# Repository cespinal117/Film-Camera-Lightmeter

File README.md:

# Film-Camera-Lightmeter
A PCB I designed to integrate a light meter onto my film camera.  
My inspiration for this was when I got my first film camera, a Cannon AE-1, I noticed the built-in light-meter was broken.  
For most of my time, I have been using my phone with a light-meter app to adjust my camera settings but that got annoying quick. 
Since I wanted to practice more PCB design, I figured the best way to get practice in and solve my issue is to make my own light meter and manufacture a PCB for it.

## PCB Features
 - Raspberry Pi Pico MCU
 - VEML7700-TR Ambient Light Sensor
 - Lipo battery charging circuit
 - Button control inputs
 - Automatic switching between USB power & Battery power
 - Static Discharge protection

## PCB Design

The PCB is a 2-layer board to minimize cost.  

It uses a Raspberry Pi Pico MCU as it was a relatively new board I was trying to learn to use. 
To power it, you can supply either USB-C for development, or a 3.7V Lipo battery.

It is still a WIP and I hope to have it manufactured soon.

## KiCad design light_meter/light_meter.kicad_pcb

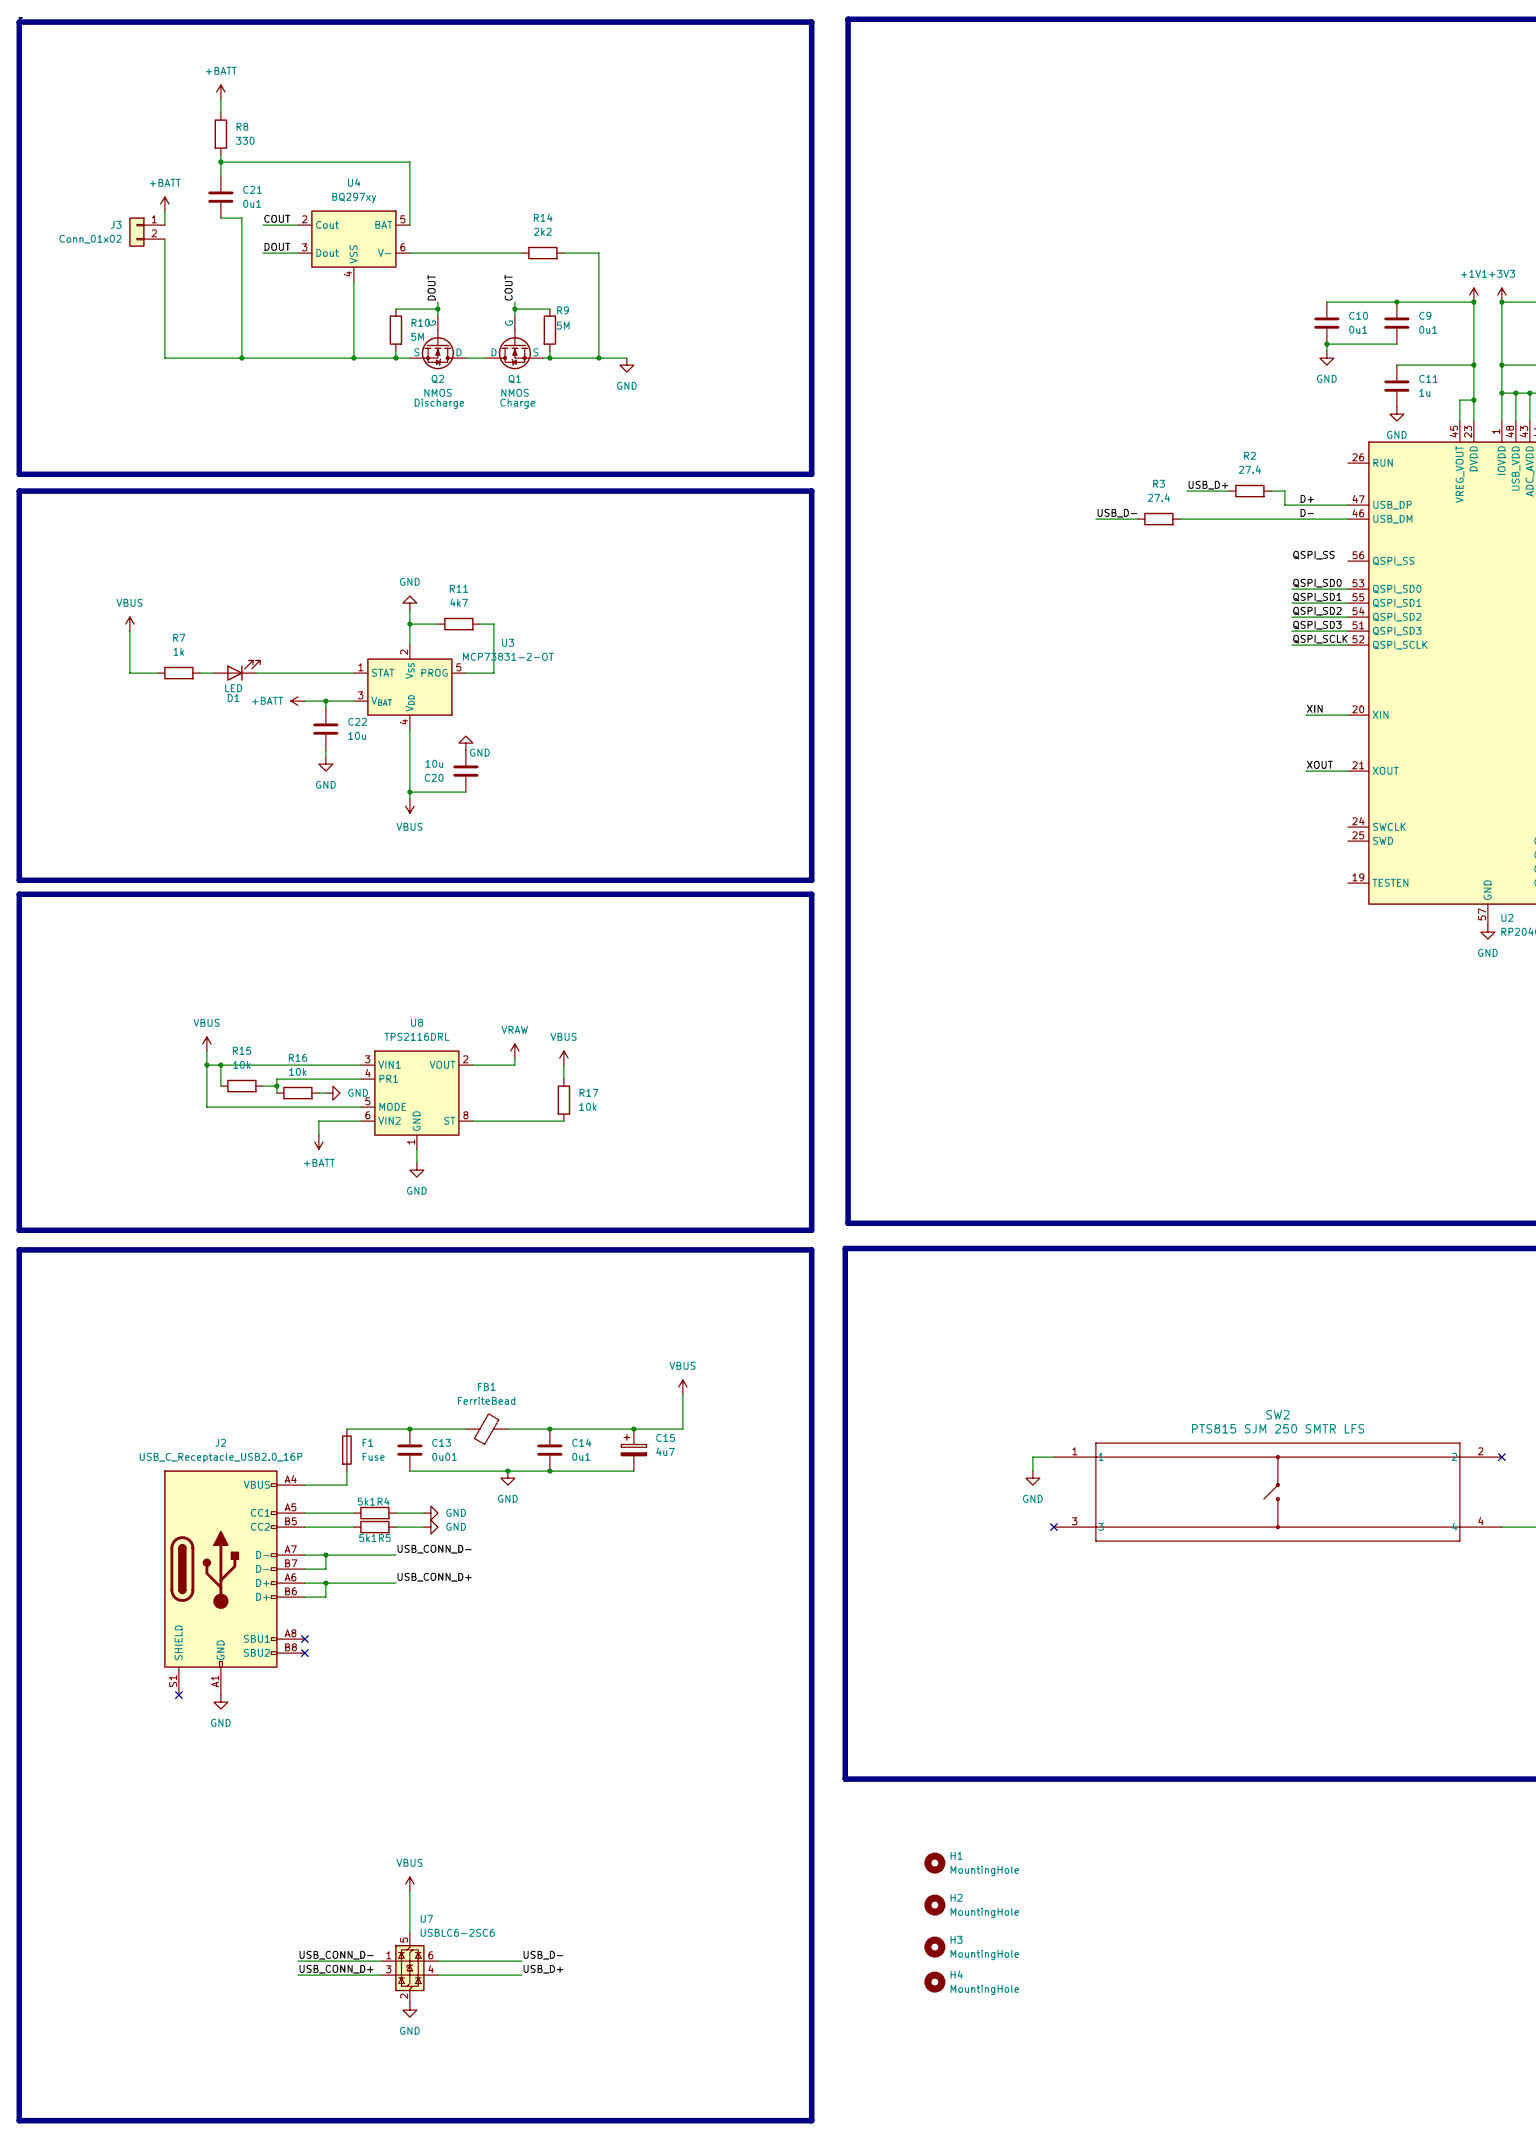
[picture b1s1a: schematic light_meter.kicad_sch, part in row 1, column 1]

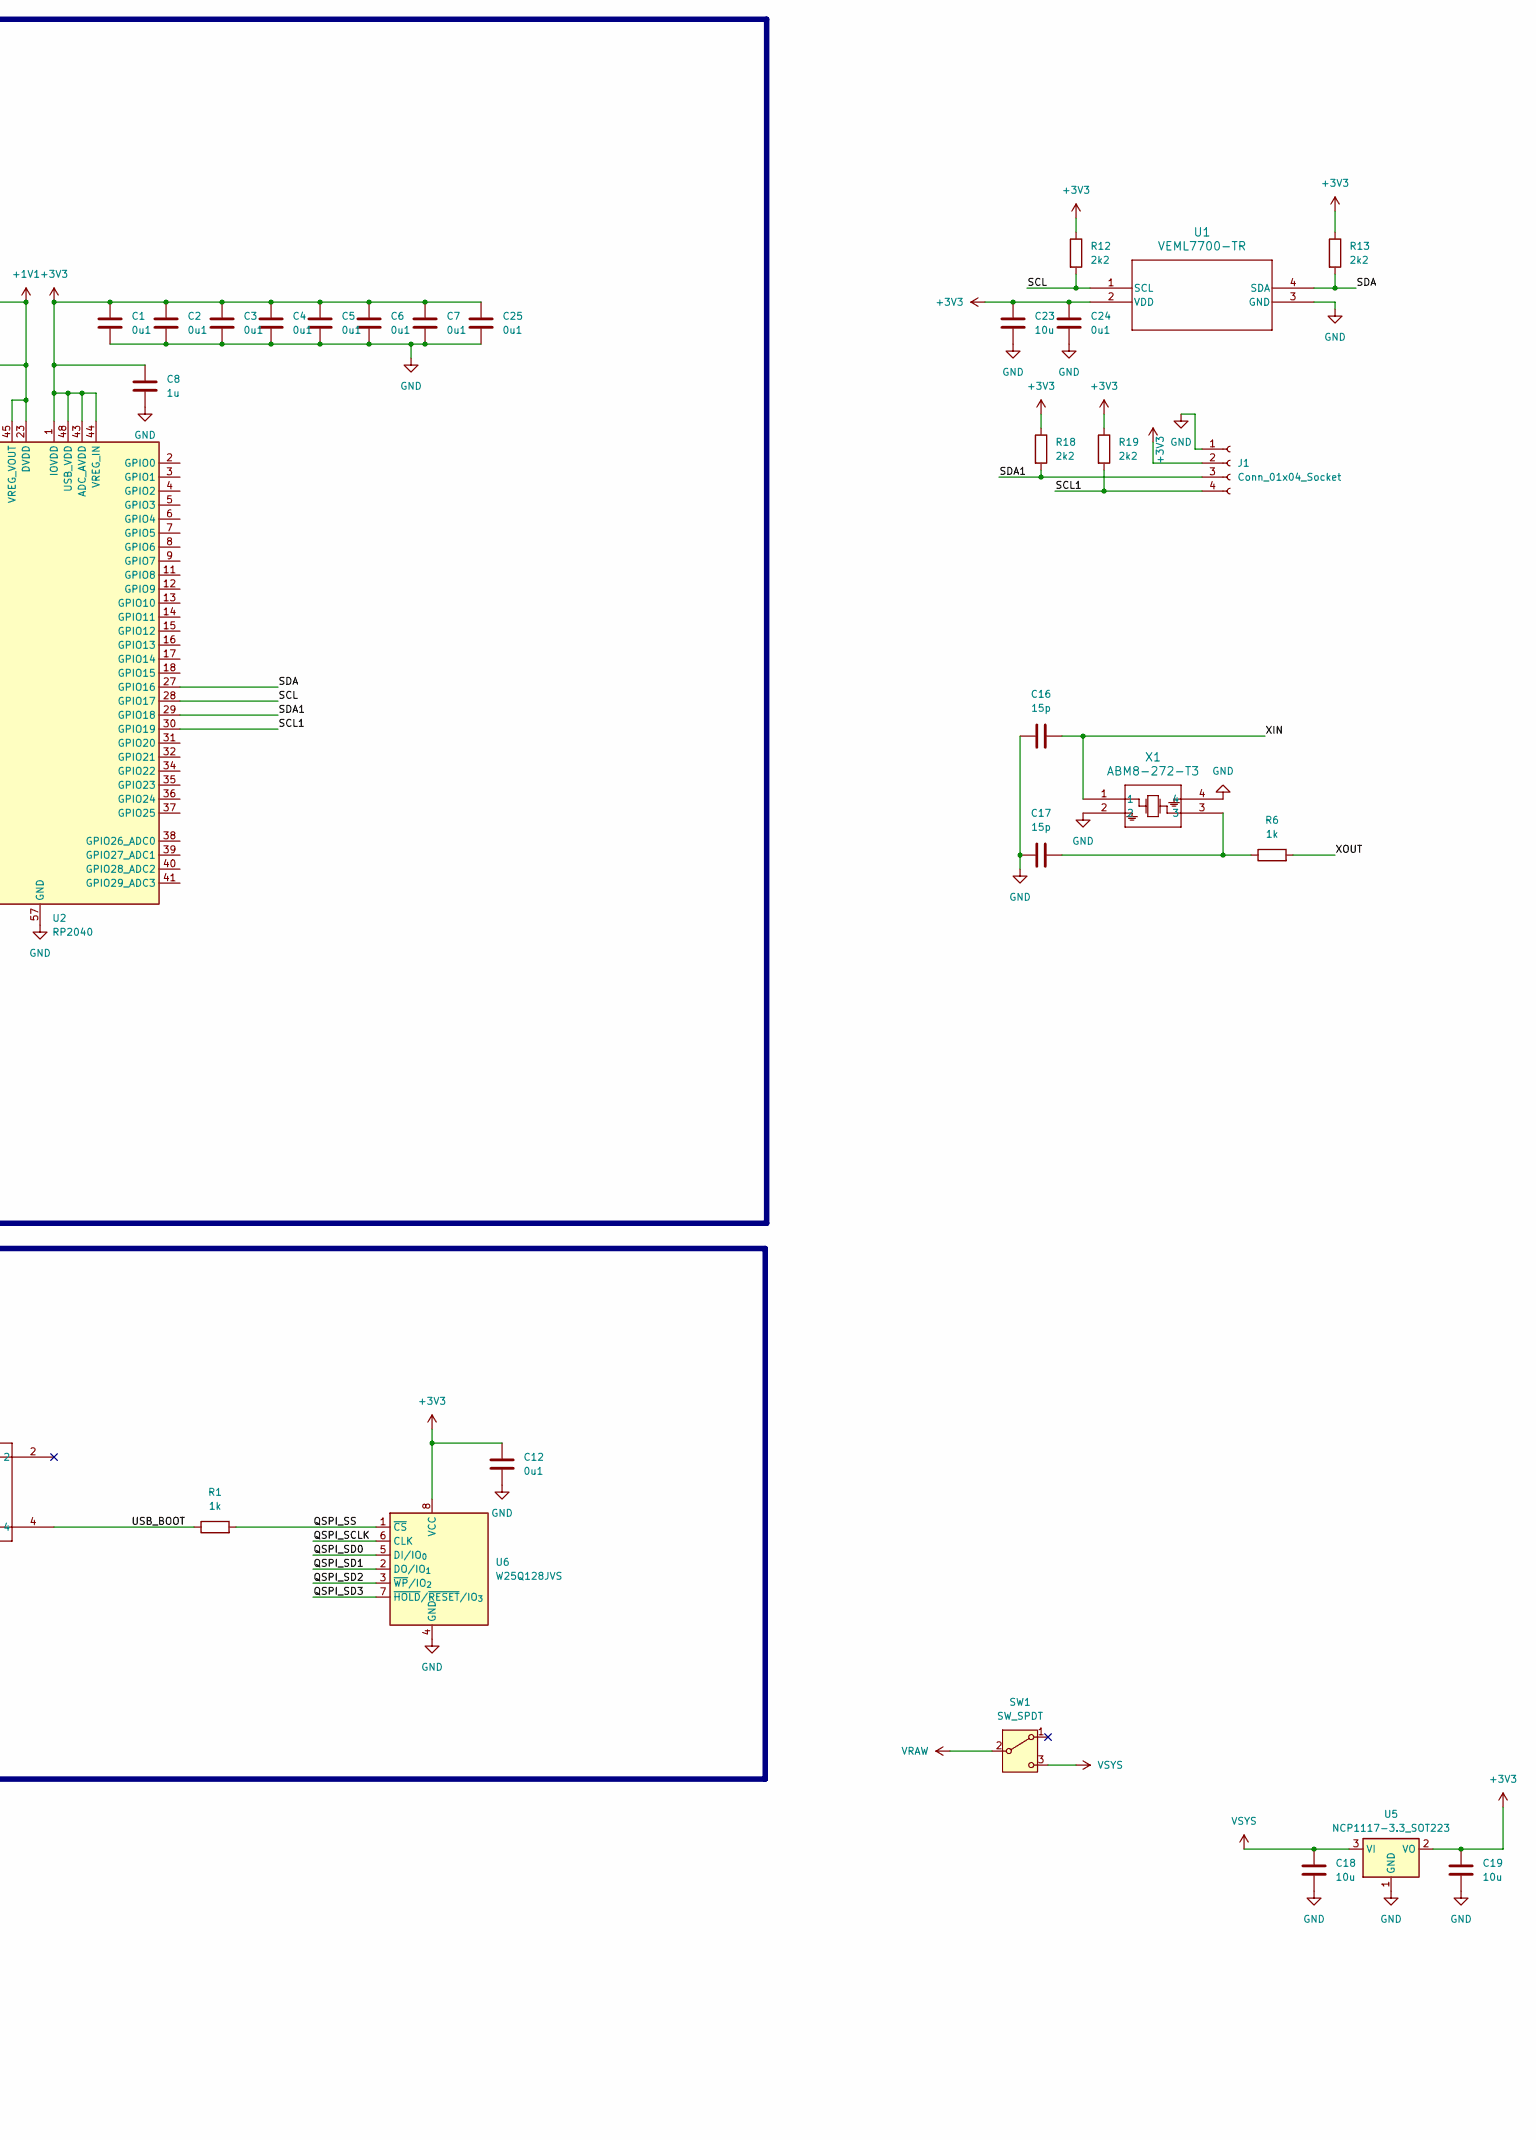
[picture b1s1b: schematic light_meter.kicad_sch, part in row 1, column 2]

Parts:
C1, C2, C3, C4, C5, C6, C7, C9, C10, C12, C14, C21, C24, C25: 0u1; C_0402_1005Metric
C8, C11: 1u; C_0402_1005Metric
C13: 0u01; C_0402_1005Metric
C15: 4u7; CP_Elec_4x5.7
C16, C17: 15p; C_0402_1005Metric
C18, C19, C20, C22: 10u; C_0603_1608Metric
C23: 10u; C_0402_1005Metric
D1: LED; LED_0603_1608Metric
F1: Fuse; Fuse_1812_4532Metric
FB1: FerriteBead; L_0603_1608Metric
H1, H2, H3, H4: MountingHole; MountingHole_2.2mm_M2
J1: Conn_01x04_Socket; JST_SH_SM04B-SRSS-TB_1x04-1MP_P1.00mm_Horizontal
J2: USB_C_Receptacle_USB2.0_16P; USB_C_Receptacle_GCT_USB4085; Part Number 2073-USB4085-GF-ATR-ND
J3: Conn_01x02; CONN_S2B-PH-K-S_JST; part number 455-1719-ND
Q1, Q2: NMOS; SOT-23-3
R1, R6: 1k; R_0402_1005Metric
R2, R3: 27.4; R_0402_1005Metric
R4, R5: 5k1; R_0402_1005Metric
R7: 1k; R_0603_1608Metric
R8: 330; R_0603_1608Metric
R9, R10: 5M; R_0402_1005Metric
R11: 4k7; R_0603_1608Metric
R12, R13, R18, R19: 2k2; R_0402_1005Metric
R14: 2k2; R_0603_1608Metric
R15, R16, R17: 10k; R_0603_1608Metric
SW1: SW_SPDT; SW_L102021ML04Q; digikey CKC5102-ND
SW2: PTS815 SJM 250 SMTR LFS; SW4_PTS815 SJM 250 SMTR LFS_CNK
U1: VEML7700-TR
U2: RP2040; QFN-56-1EP_7x7mm_P0.4mm_EP3.2x3.2mm
U3: MCP73831-2-OT; SOT-23-5
U4: BQ297xy; WSON-6_1.5x1.5mm_P0.5mm
U5: NCP1117-3.3_SOT223; SOT-223-3_TabPin2
U6: W25Q128JVS; SOIC-8_5.3x5.3mm_P1.27mm
U7: USBLC6-2SC6; SOT-23-6
U8: TPS2116DRL; SOT-583-8
X1: ABM8-272-T3; ABM8-272-T3_ABR

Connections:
+1V1: C9.1, C10.1, C11.1, U2.23 (DVDD), U2.45 (VREG_VOUT), U2.50 (DVDD)
+3V3: C1.1, C2.1, C3.1, C4.1, C5.1, C6.1, C7.1, C8.1, C12.1, C19.1, C23.1, C24.1, C25.1, J1.2, R12.1, R13.1, R18.1, R19.1, U1.2 (VDD), U2.1 (IOVDD), U2.10 (IOVDD), U2.22 (IOVDD), U2.33 (IOVDD), U2.42 (IOVDD), U2.43 (ADC_AVDD), U2.44 (VREG_IN), U2.48 (USB_VDD), U2.49 (IOVDD), U5.2 (VO), U6.8 (VCC)
+BATT: C22.1, J3.1, R8.1, U3.3 (V_{BAT}), U8.6 (VIN2)
/COUT: Q1.2 (G), R9.1, U4.2 (Cout)
/D+: R2.2, U2.47 (USB_DP)
/D-: R3.2, U2.46 (USB_DM)
/DOUT: Q2.2 (G), R10.1, U4.3 (Dout)
/QSPI_SCLK: U2.52 (QSPI_SCLK), U6.6 (CLK)
/QSPI_SD0: U2.53 (QSPI_SD0), U6.5 (DI/IO_{0})
/QSPI_SD1: U2.55 (QSPI_SD1), U6.2 (DO/IO_{1})
/QSPI_SD2: U2.54 (QSPI_SD2), U6.3 (~WP/IO_{2})
/QSPI_SD3: U2.51 (QSPI_SD3), U6.7 (~HOLD/~RESET/IO_{3})
/QSPI_SS: R1.2, U6.1 (~CS)
/SCL: R12.2, U1.1 (SCL), U2.28 (GPIO17)
/SCL1: J1.4, R19.2, U2.30 (GPIO19)
/SDA: R13.2, U1.4 (SDA), U2.27 (GPIO16)
/SDA1: J1.3, R18.2, U2.29 (GPIO18)
/USB_BOOT: R1.1, SW2.4
/USB_CONN_D+: J2.A6 (D+), J2.B6 (D+), U7.3 (I/O2)
/USB_CONN_D-: J2.A7 (D-), J2.B7 (D-), U7.1 (I/O1)
/USB_D+: R2.1, U7.4 (I/O2)
/USB_D-: R3.1, U7.6 (I/O1)
/XIN: C16.2, U2.20 (XIN), X1.1
/XOUT: R6.2, U2.21 (XOUT)
GND: C1.2, C2.2, C3.2, C4.2, C5.2, C6.2, C7.2, C8.2, C9.2, C10.2, C11.2, C12.2, C13.2, C14.2, C15.2, C16.1, C17.1, C18.2, C19.2, C20.2, C22.2, C23.2, C24.2, C25.2, J1.1, J2.A1 (GND), J2.A12 (GND), J2.B1 (GND), J2.B12 (GND), Q1.3 (S), R4.2, R5.2, R9.2, R11.1, R14.2, R16.2, SW2.1, U1.3 (GND), U2.57 (GND), U3.2 (V_{SS}), U5.1 (GND), U6.4 (GND), U7.2 (GND), U8.1 (GND), X1.2, X1.4
unnamed: C13.1, F1.1, FB1.1
unnamed: C17.2, R6.1, X1.3
unnamed: D1.2 (A), R7.2
unnamed: D1.1 (K), U3.1 (STAT)
unnamed: F1.2, J2.A4 (VBUS), J2.A9 (VBUS), J2.B4 (VBUS), J2.B9 (VBUS)
unnamed: J2.A5 (CC1), R4.1
unnamed: J2.B5 (CC2), R5.1
unnamed: C21.2, J3.2, Q2.3 (S), R10.2, U4.4 (VSS)
unnamed: Q1.1 (D), Q2.1 (D)
unnamed: R11.2, U3.5 (PROG)
unnamed: C21.1, R8.2, U4.5 (BAT)
unnamed: R14.1, U4.6 (V-)
unnamed: R15.2, R16.1, U8.4 (PR1)
unnamed: R17.2, U8.8 (ST)
VBUS: C14.1, C15.1, C20.1, FB1.2, R7.1, R15.1, R17.1, U3.4 (V_{DD}), U7.5 (VBUS), U8.3 (VIN1), U8.5 (MODE)
VRAW: SW1.2 (B), U8.2 (VOUT), U8.7 (VOUT)
VSYS: C18.1, SW1.3 (C), U5.3 (VI)

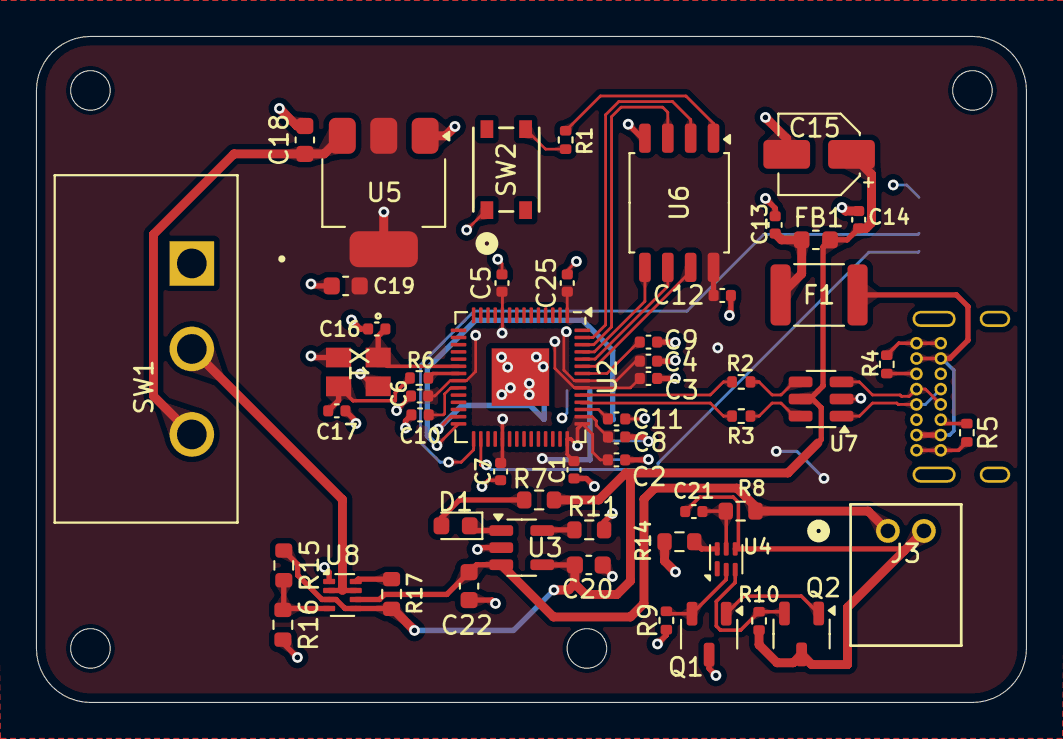
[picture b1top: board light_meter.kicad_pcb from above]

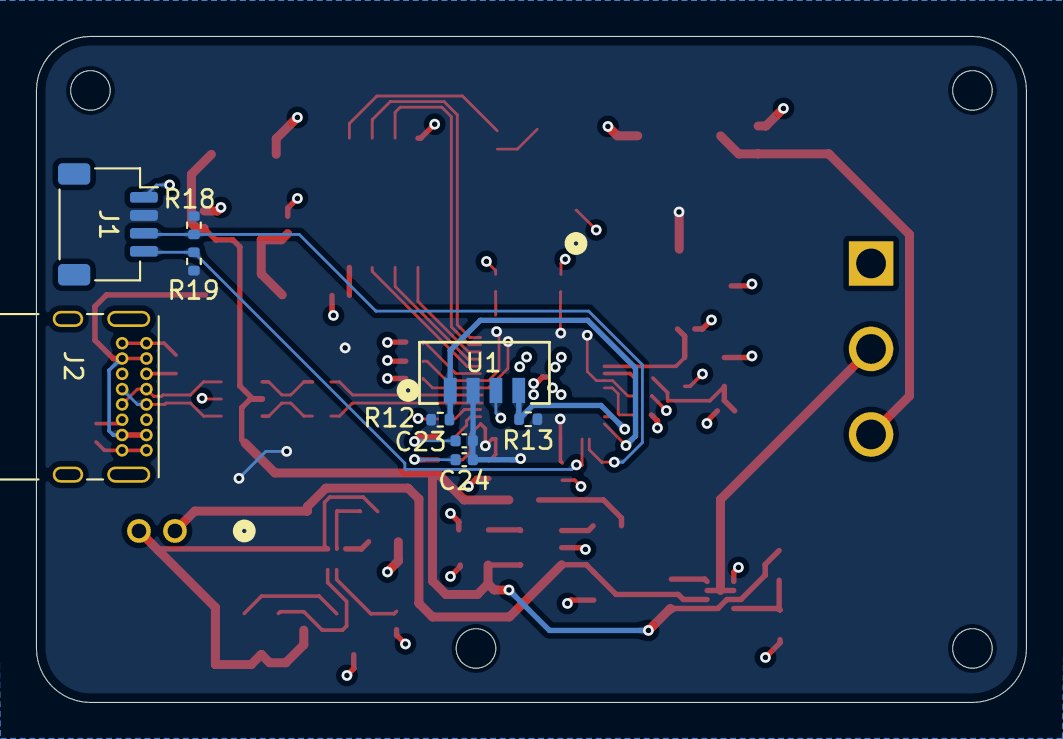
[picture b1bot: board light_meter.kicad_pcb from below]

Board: 4 copper layers, 55.0 x 37.0 mm, 67 parts (9 on the bottom side), 42 nets.

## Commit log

2025-12-03 added screenshots
2025-12-03 renamed files
